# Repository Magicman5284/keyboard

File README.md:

Welcome to my Keypad!

This is the project that I made for the 3rd week of the Hack Club Half-Life program. 
This is what they had a the beginner project, but a made a couple of modifications to make it my own!

One of the major changes I made was adding more keys so that on mine there is a while octave of notes to choose from instead of only 7. 

I put the "This is NOT a trumpet" message on the board because I play the trumpet, and I needed a way to not get confused on which instrument I was playing. 

I also added a whole bunch of buttons to keyboard that can be configured in software to do a whole bunch of different things!

BOM:
| Item                     | Qty | Supplier   | Cost/item | Total Cost | link                                                                                                                                                                                                                                                                                                                                                                                                                                                                                                                                                                                                                                                                                                                                                                               |
|--------------------------|-----|------------|-----------|------------|------------------------------------------------------------------------------------------------------------------------------------------------------------------------------------------------------------------------------------------------------------------------------------------------------------------------------------------------------------------------------------------------------------------------------------------------------------------------------------------------------------------------------------------------------------------------------------------------------------------------------------------------------------------------------------------------------------------------------------------------------------------------------------|
| MPR121 board             | 1   | Aliexpress | $2.27     | $2.27      | https://www.aliexpress.us/item/3256809629663052.html?src=google&src=google&albch=shopping&acnt=708-803-3821&isdl=y&slnk=&plac=&mtctp=&albbt=Google_7_shopping&aff_platform=google&aff_short_key=UneMJZVf&gclsrc=aw.ds&albagn=888888&ds_e_adid=&ds_e_matchtype=&ds_e_device=c&ds_e_network=x&ds_e_product_group_id=&ds_e_product_id=en3256809629663052&ds_e_product_merchant_id=5341214484&ds_e_product_country=US&ds_e_product_language=en&ds_e_product_channel=online&ds_e_product_store_id=&ds_url_v=2&albcp=19558607238&albag=&isSmbAutoCall=false&needSmbHouyi=false&gad_source=1&gad_campaignid=19566915268&gbraid=0AAAAAD6I-hFRbk__bBNphYlmqWvxhbHE9&gclid=Cj0KCQjwrvHWBhDKARIsABmp7h3YdkziDnZzFii8UzGrs1lW5l4X8nnago7vmHd0GYeniLt7o9jnIPIaAjVhEALw_wcB&gatewayAdapt=glo2usa |
| Keyboard Switches        | 1   | Aliexpress | $7.65     | $7.65      | https://www.aliexpress.us/item/3256808464776326.html?spm=a2g0o.productlist.main.2.35d43c5f7T42yJ&algo_pvid=deb7c7e9-e417-48e4-9d45-300d3860da87&algo_exp_id=deb7c7e9-e417-48e4-9d45-300d3860da87-1&pdp_ext_f=%7B%22order%22%3A%22522%22%2C%22eval%22%3A%221%22%2C%22fromPage%22%3A%22search%22%7D&pdp_npi=6%40dis%21USD%217.65%217.65%21%21%2150.76%2150.76%21%402103292b17928908490096376e0fa4%2112000046099032274%21sea%21US%212783459362%21X%211%210%21n_tag%3A-29919%3Bd%3Abaf43391%3Bm03_new_user%3A-29895&curPageLogUid=Y2Ypb88maaa2&utparam-url=scene%3Asearch%7Cquery_from%3A%7Cx_object_id%3A1005008651091078%7C_p_origin_prod%3A                                                                                                                                         |
| Rotary encoder           | 1   | Aliexpress | $3.59     | $3.59      | https://www.aliexpress.us/item/3256804721769785.html?spm=a2g0o.productlist.main.9.6db7435fPfLQBy&algo_pvid=7f28f6de-0e1a-418d-8022-0250c71d8e6d&algo_exp_id=7f28f6de-0e1a-418d-8022-0250c71d8e6d-8&pdp_ext_f=%7B%22order%22%3A%22756%22%2C%22eval%22%3A%221%22%2C%22fromPage%22%3A%22search%22%7D&pdp_npi=6%40dis%21USD%212.55%212.55%21%21%2116.92%2116.92%21%402103292b17928909479387847e0d94%2112000030980447524%21sea%21US%212783459362%21X%211%210%21n_tag%3A-29919%3Bd%3Abaf43391%3Bm03_new_user%3A-29895&curPageLogUid=Gt6RJs9ZGIBk&utparam-url=scene%3Asearch%7Cquery_from%3A%7Cx_object_id%3A1005004908084537%7C_p_origin_prod%3A                                                                                                                                         |
| ESP32-S3-Zero            | 1   | Aliexpress | $3.67     | $3.67      | https://www.aliexpress.us/item/3256807949476561.html?spm=a2g0o.productlist.main.2.fad61076dBxKml&algo_pvid=76d142b5-28e0-4da4-bdd9-70a0e54ffb03&algo_exp_id=76d142b5-28e0-4da4-bdd9-70a0e54ffb03-1&pdp_ext_f=%7B%22order%22%3A%22683%22%2C%22eval%22%3A%221%22%2C%22fromPage%22%3A%22search%22%7D&pdp_npi=6%40dis%21USD%214.32%213.32%21%21%214.32%213.32%21%402101e80f17928912369963459e1068%2112000051614441514%21sea%21US%212783459362%21X%211%210%21n_tag%3A-29919%3Bd%3Abaf43391%3Bm03_new_user%3A-29895%3BpisId%3A5000000219603055&curPageLogUid=zKdormEAERkf&utparam-url=scene%3Asearch%7Cquery_from%3A%7Cx_object_id%3A1005008135791313%7C_p_origin_prod%3A                                                                                                                |
| PCB                      | 1   | JLCPCB     | $16.67    | $16.67     | https://jlcpcb.com/                                                                                                                                                                                                                                                                                                                                                                                                                                                                                                                                                                                                                                                                                                                                                                |
| Estimated total shipping | 1   | $0.00      |           |            |                                                                                                                                                                                                                                                                                                                                                                                                                                                                                                                                                                                                                                                                                                                                                                                    |

About:
This is a capacitive Midi keyboard with a total of 12 keys
pressing a key plays a distinct sound correlating with that note
It features 9 switches and a rotary encoder to control various functions which can be configured in software. 

Images:

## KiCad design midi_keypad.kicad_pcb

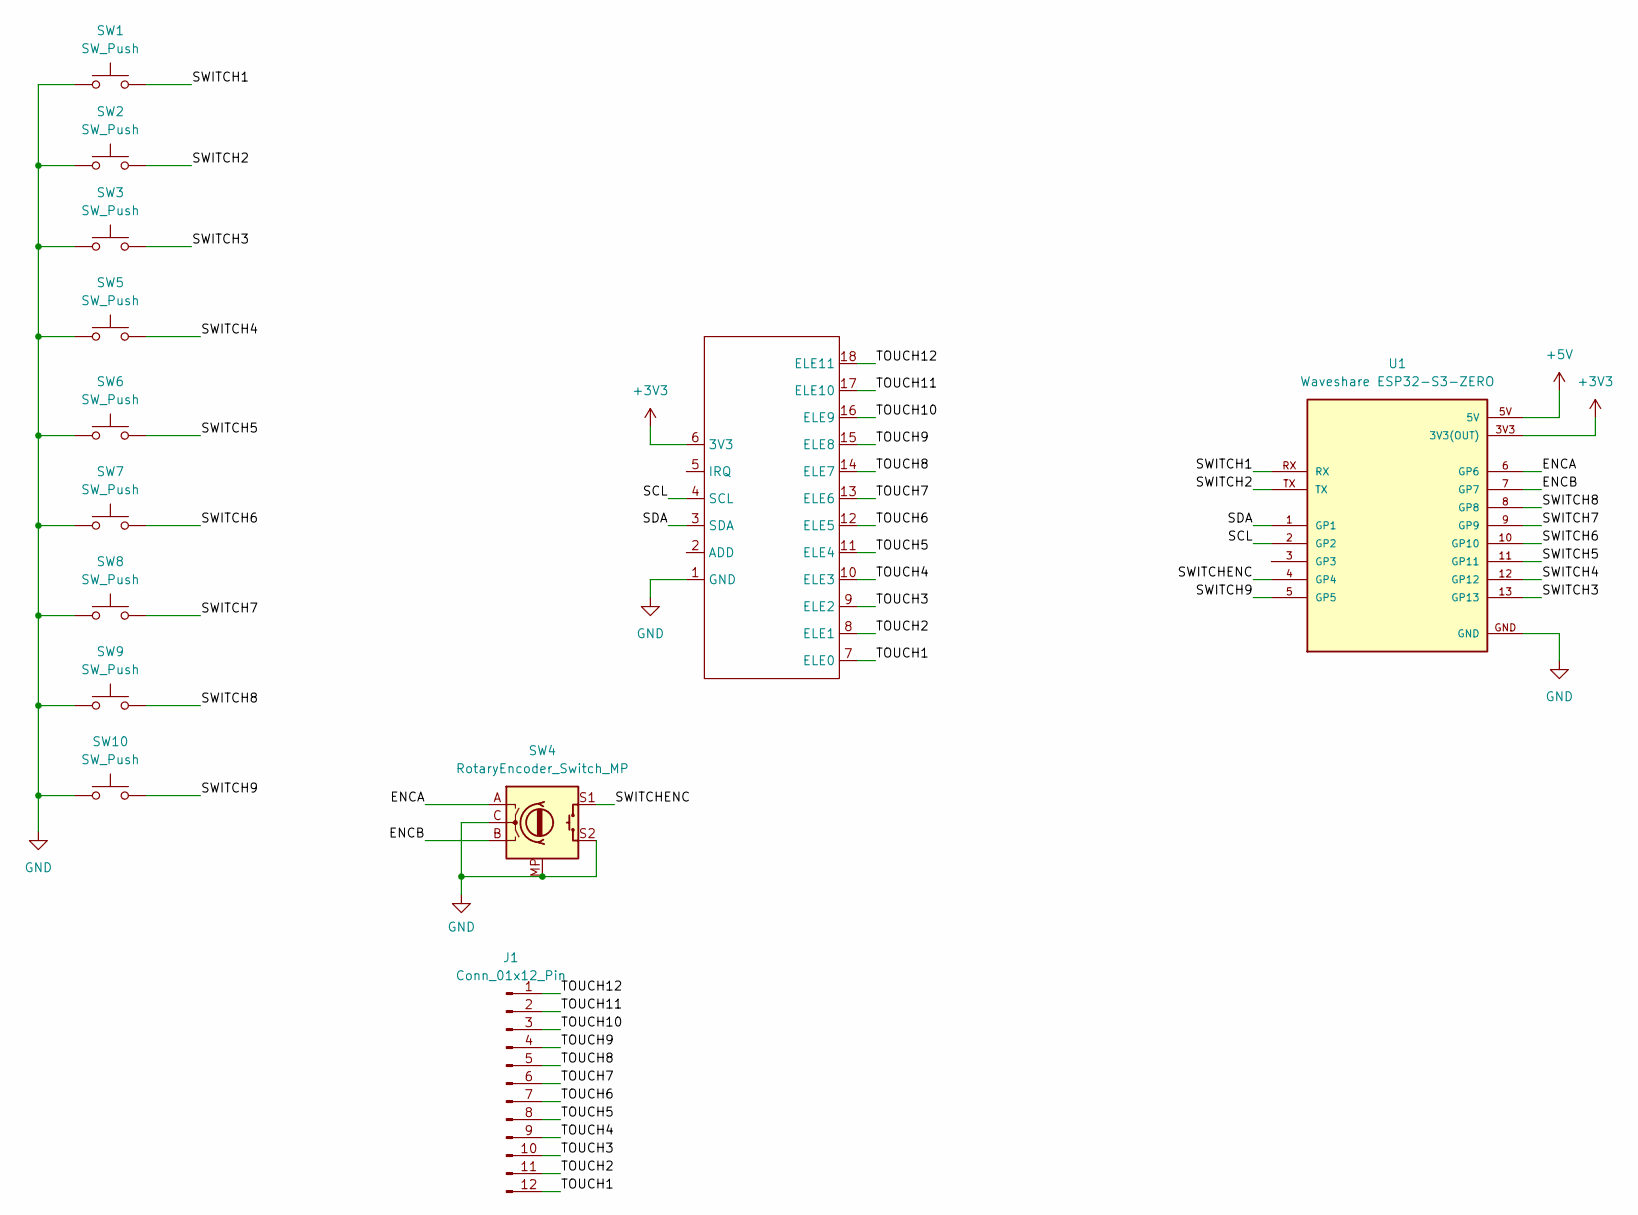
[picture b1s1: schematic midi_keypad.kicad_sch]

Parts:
J1: Conn_01x12_Pin; Keyboard
SW1, SW2, SW3, SW5, SW6, SW7, SW8, SW9, SW10: SW_Push; Kailh Choc Low-Profile Switches
SW4: RotaryEncoder_Switch_MP; RotaryEncoder_Alps_EC11E-Switch_Vertical_H20mm
U1: Waveshare ESP32-S3-ZERO; Waveshare ESP32-S3-Zero; PARTREV NA
U2: MPR121_Breakout_claude_Flipped

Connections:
+3V3: U1.3V3 (3V3(OUT)), U2.6 (3V3)
+5V: U1.5V
/ENCA: SW4.A, U1.6 (GP6)
/ENCB: SW4.B, U1.7 (GP7)
/SCL: U1.2 (GP2), U2.4 (SCL)
/SDA: U1.1 (GP1), U2.3 (SDA)
/SWITCH1: SW1.2, U1.RX
/SWITCH2: SW2.2, U1.TX
/SWITCH3: SW3.2, U1.13 (GP13)
/SWITCH4: SW5.2, U1.12 (GP12)
/SWITCH5: SW6.2, U1.11 (GP11)
/SWITCH6: SW7.2, U1.10 (GP10)
/SWITCH7: SW8.2, U1.9 (GP9)
/SWITCH8: SW9.2, U1.8 (GP8)
/SWITCH9: SW10.2, U1.5 (GP5)
/SWITCHENC: SW4.S1, U1.4 (GP4)
/TOUCH1: J1.12, U2.7 (ELE0)
/TOUCH2: J1.11, U2.8 (ELE1)
/TOUCH3: J1.10, U2.9 (ELE2)
/TOUCH4: J1.9, U2.10 (ELE3)
/TOUCH5: J1.8, U2.11 (ELE4)
/TOUCH6: J1.7, U2.12 (ELE5)
/TOUCH7: J1.6, U2.13 (ELE6)
/TOUCH8: J1.5, U2.14 (ELE7)
/TOUCH9: J1.4, U2.15 (ELE8)
/TOUCH10: J1.3, U2.16 (ELE9)
/TOUCH11: J1.2, U2.17 (ELE10)
/TOUCH12: J1.1, U2.18 (ELE11)
GND: SW1.1, SW2.1, SW3.1, SW4.C, SW4.MP, SW4.S2, SW5.1, SW6.1, SW7.1, SW8.1, SW9.1, SW10.1, U1.GND, U2.1 (GND)

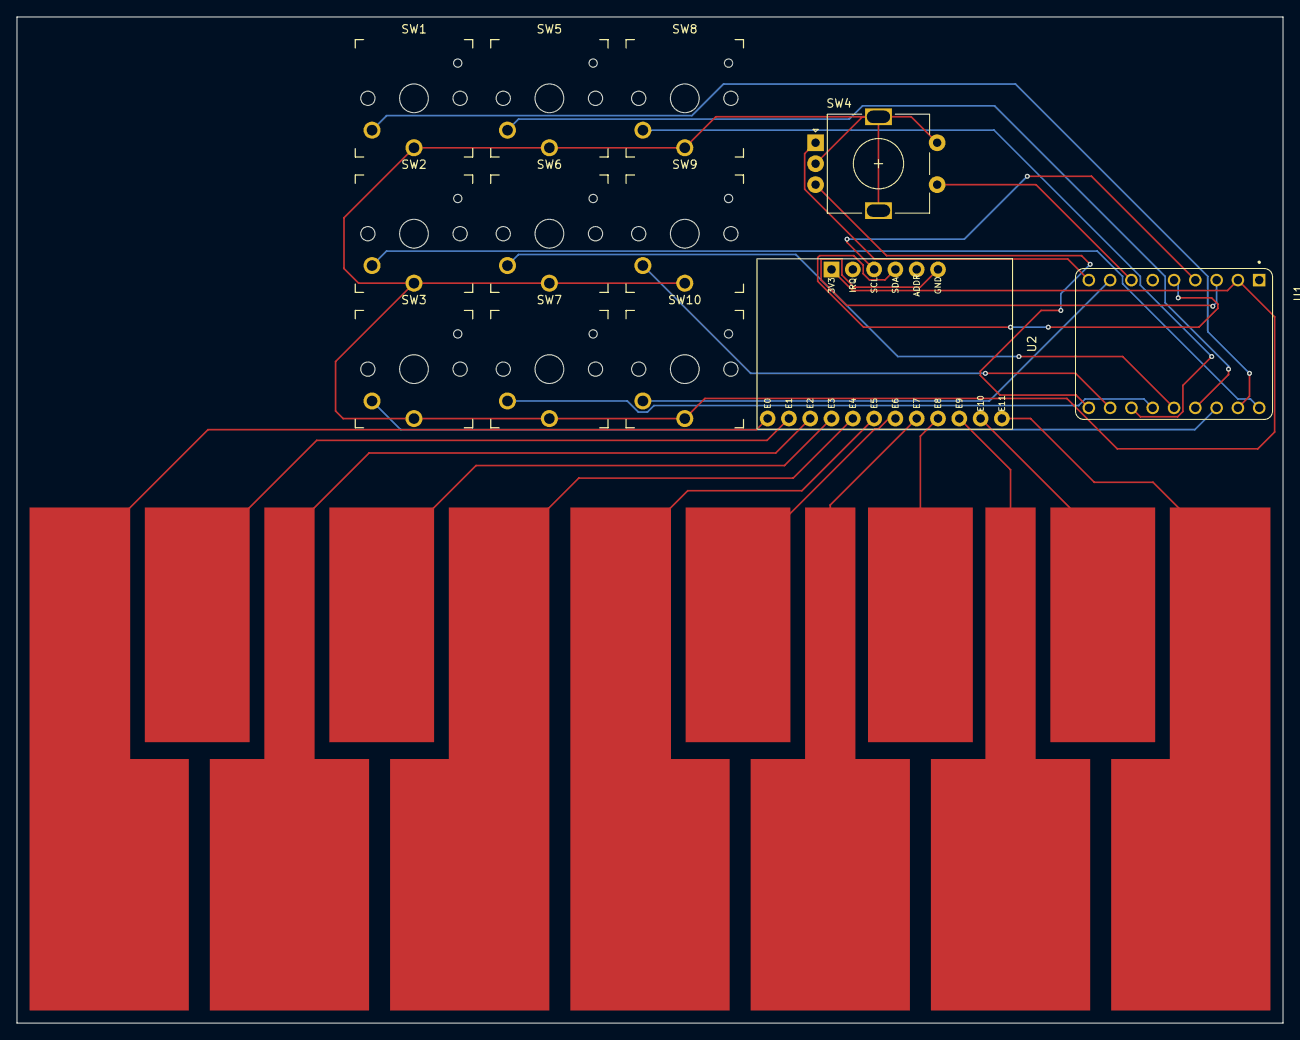
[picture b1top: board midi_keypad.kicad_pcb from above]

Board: 2 copper layers, 151.0 x 120.0 mm, 13 parts (0 on the bottom side), 28 nets.
